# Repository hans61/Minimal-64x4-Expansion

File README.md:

# Minimal-64x4-Expansion

Hardware
https://github.com/hans61/Minimal-64x4-Expansion/tree/main/hardware

Software
https://github.com/hans61/Minimal-64x4-Expansion/tree/main/software

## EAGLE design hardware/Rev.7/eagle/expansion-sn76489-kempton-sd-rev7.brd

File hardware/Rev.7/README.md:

# Minimal-64x4 Expansion Rev.7

Revision 7 extends the previous one with a power ON reset based on a NE555.

Revision 6: https://github.com/hans61/Minimal-64x4-Expansion/tree/main/hardware/Rev.6

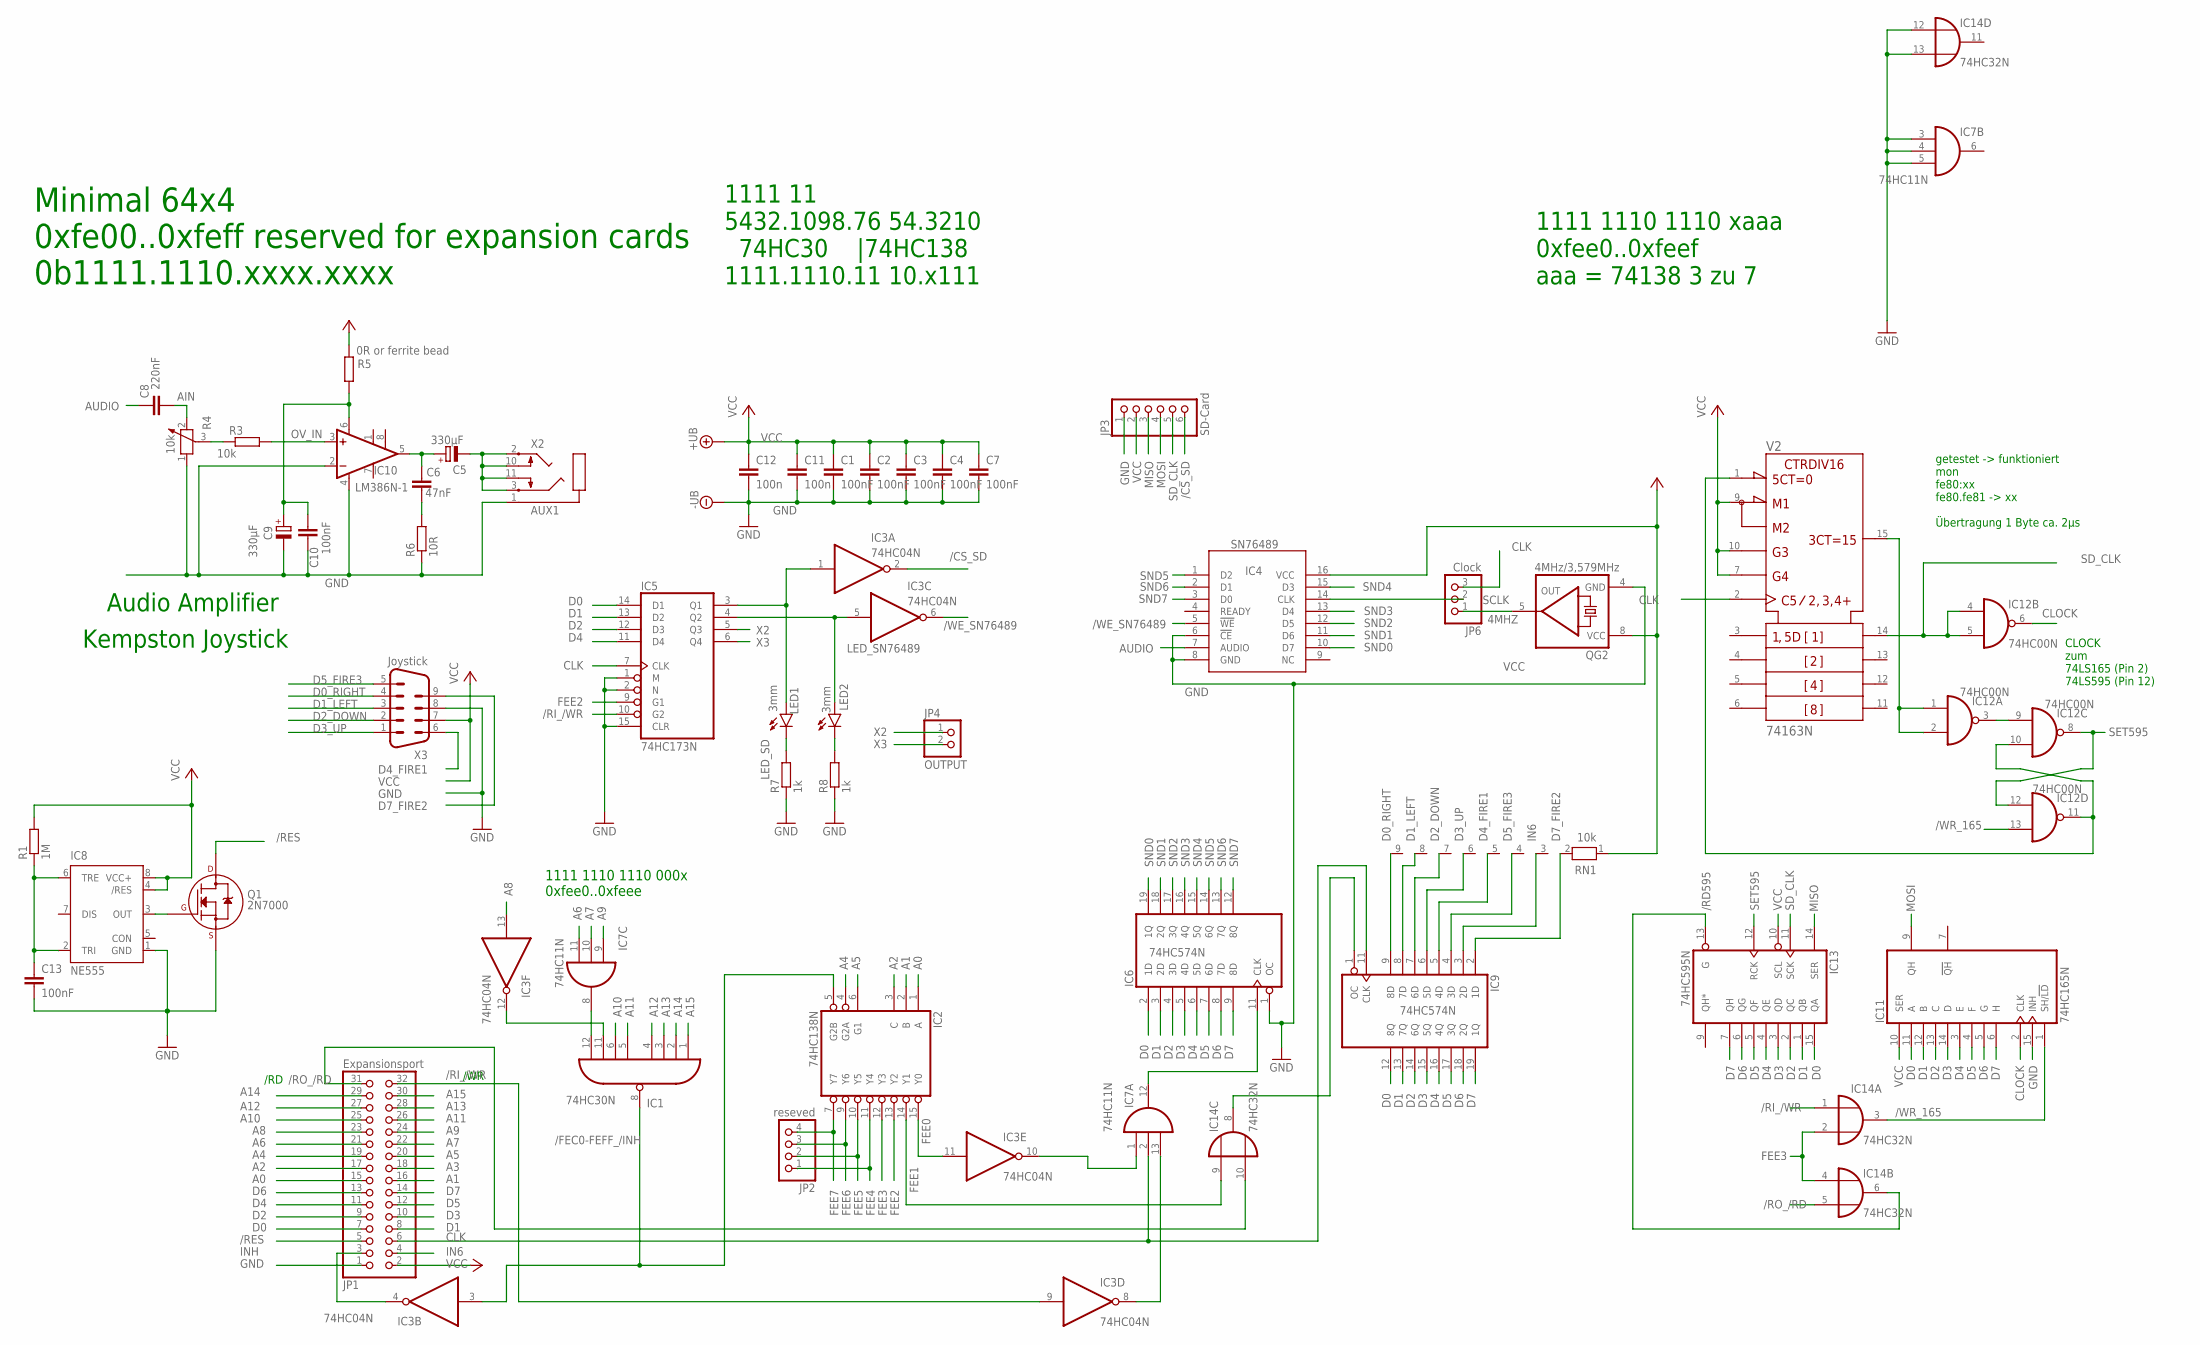
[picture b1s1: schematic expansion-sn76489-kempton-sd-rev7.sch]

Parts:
C1, C2, C3, C4, C7, C10: 100nF; C050-025X075
C5, C9: 330µF; E2,5-7
C6: 47nF; C050-025X075
C8: 220nF; C050-025X075
C11, C12: 100n; C050-025X075
C13: 100nF; C050-030X075
IC1: 74HC30N; DIL14
IC2: 74HC138N; DIL16
IC3: 74HC04N; DIL14
IC4: SN76489; ALEX-PARTS_DIL16
IC5: 74HC173N; DIL16
IC6, IC9: 74HC574N; DIL20
IC7: 74HC11N; DIL14
IC8: NE555; DIL-08
IC10: LM386N-1; DIL08
IC11: 74HC165N; DIL16
IC12: 74HC00N; DIL14
IC13: 74HC595N; DIL16
IC14: 74HC32N; DIL14
JP1: Expansionsport; 2X16
JP2: reseved; 1X04
JP3: SD-Card; 1X06
JP4: OUTPUT; 1X02
JP6: Clock; 1X03
LED1, LED2: 3mm; LED3MM
Q1: 2N7000; TO-92
QG2: 4MHz/3,579MHz; DIL08S
R1: 1M; 0207/10
R3: 10k; 0207/10
R4: 10k; PT-10S
R5: 0R or ferrite bead; 0207/10
R6: 10R; 0207/10
R7, R8: 1k; 0207/2V
RN1: 10k; RN-9
V2: 74163N; DIL16
X2: AUX1; SJ1-352XN
X3: Joystick; 182-009-MALE

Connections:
4MHZ: JP6.1, QG2.5 (OUT)
/CS_SD: IC3.2 (O), JP3.6
/FEC0-FEFF_/INH: IC1.8 (O), IC2.5 (G2B), IC3.3 (I)
/RD595: IC13.13 (G), IC14.6 (O)
/RES: JP1.5, Q1.3 (D)
/RI_/WR: IC3.9 (I), IC5.10 (G2), IC14.1 (I0), JP1.32
/RO_/RD: IC14.5 (I1), IC14.10 (I1), JP1.31
/WE_SN76489: IC3.6 (O), IC4.5 (!WE)
/WR_165: IC11.1 (SH/!LD), IC12.13 (I1), IC14.3 (O)
A0: IC2.1 (A), JP1.15
A1: IC2.2 (B), JP1.16
A2: IC2.3 (C), JP1.17
A3: JP1.18
A4: IC2.4 (G2A), JP1.19
A5: IC2.6 (G1), JP1.20
A6: IC7.11 (I2), JP1.21
A7: IC7.10 (I1), JP1.22
A8: IC3.13 (I), JP1.23
A9: IC7.9 (I0), JP1.24
A10: IC1.6 (I5), JP1.25
A11: IC1.5 (I4), JP1.26
A12: IC1.4 (I3), JP1.27
A13: IC1.3 (I2), JP1.28
A14: IC1.2 (I1), JP1.29
A15: IC1.1 (I0), JP1.30
AIN: C8.2, R4.2
AUDIO: C8.1, IC4.7 (AUDIO)
AUXOUT1: C5.-, X2.2, X2.3, X2.10, X2.11
AVCC: C9.+, C10.1, IC10.6 (VS), R5.1
CLK: IC5.7 (CLK), IC7.2 (I1), IC9.11 (CLK), JP1.6, JP6.3, V2.2 (CLK)
CLOCK: IC11.2 (CLK), IC12.6 (O)
D0: IC5.14 (D1), IC6.2 (1D), IC9.12 (8Q), IC11.11 (A), IC13.15 (QA), JP1.7
D0_RIGHT: IC9.9 (8D), RN1.9, X3.4
D1: IC5.13 (D2), IC6.3 (2D), IC9.13 (7Q), IC11.12 (B), IC13.1 (QB), JP1.8
D1_LEFT: IC9.8 (7D), RN1.8, X3.3
D2: IC5.12 (D3), IC6.4 (3D), IC9.14 (6Q), IC11.13 (C), IC13.2 (QC), JP1.9
D2_DOWN: IC9.7 (6D), RN1.7, X3.2
D3: IC6.5 (4D), IC9.15 (5Q), IC11.14 (D), IC13.3 (QD), JP1.10
D3_UP: IC9.6 (5D), RN1.6, X3.1
D4: IC5.11 (D4), IC6.6 (5D), IC9.16 (4Q), IC11.3 (E), IC13.4 (QE), JP1.11
D4_FIRE1: IC9.5 (4D), RN1.5, X3.6
D5: IC6.7 (6D), IC9.17 (3Q), IC11.4 (F), IC13.5 (QF), JP1.12
D5_FIRE3: IC9.4 (3D), RN1.4, X3.5
D6: IC6.8 (7D), IC9.18 (2Q), IC11.5 (G), IC13.6 (QG), JP1.13
D7: IC6.9 (8D), IC9.19 (1Q), IC11.6 (H), IC13.7 (QH), JP1.14
D7_FIRE2: IC9.2 (1D), RN1.2, X3.9
FEE0: IC2.15 (Y0), IC3.11 (I)
FEE1: IC2.14 (Y1), IC14.9 (I0)
FEE2: IC2.13 (Y2), IC5.9 (G1)
FEE3: IC2.12 (Y3), IC14.2 (I1), IC14.4 (I0)
FEE4: IC2.11 (Y4), JP2.1
FEE5: IC2.10 (Y5), JP2.2
FEE6: IC2.9 (Y6), JP2.3
FEE7: IC2.7 (Y7), JP2.4
GND: C1.2, C2.2, C3.2, C4.2, C7.2, C9.-, C10.2, C11.2, C12.2, C13.2, IC1.7 (GND), IC2.8 (GND), IC3.7 (GND), IC4.6 (!CE), IC4.8 (GND), IC5.1 (M), IC5.2 (N), IC5.8 (GND), IC5.15 (CLR), IC6.1 (OC), IC6.10 (GND), IC7.3 (I0), IC7.4 (I1), IC7.5 (I2), IC7.7 (GND), IC8.1 (GND), IC9.10 (GND), IC10.2 (-IN), IC10.4 (GND), IC11.8 (GND), IC11.15 (INH), IC12.7 (GND), IC13.8 (GND), IC14.7 (GND), IC14.12 (I0), IC14.13 (I1), JP1.1, JP3.1, Q1.1 (S), QG2.4 (GND), R4.1, R6.1, R7.1, R8.1, V2.8 (-UB), X2.1, X3.8
IN6: IC9.3 (2D), JP1.4, RN1.3
INH: IC3.4 (O), JP1.3
INPUT_EN: IC9.1 (OC), IC14.8 (O)
LED_SD: IC3.1 (I), IC5.3 (Q1), LED1.A
LED_SN76489: IC3.5 (I), IC5.4 (Q2), LED2.A
MISO: IC13.14 (SER), JP3.3
MOSI: IC11.9 (QH), JP3.4
unnamed: LED2.K (C), R8.2
unnamed: IC3.10 (O), IC7.1 (I0)
unnamed: IC1.12 (I7), IC7.8 (O)
unnamed: C13.1, IC8.2 (TRI), IC8.6 (TRE), R1.1
unnamed: IC8.3 (OUT), Q1.2 (G)
unnamed: C6.2, R6.2
unnamed: IC12.1 (I0), IC12.2 (I1), V2.15 (RCO)
unnamed: R3.1, R4.3
unnamed: IC12.10 (I1), IC12.11 (O), V2.1 (!CLR)
unnamed: IC12.3 (O), IC12.9 (I0)
unnamed: LED1.K (C), R7.2
unnamed: IC1.11 (I6), IC3.12 (O)
OV_IN: IC10.3 (+IN), R3.2
R2C2C3: C5.+, C6.1, IC10.5 (OUT)
RI_WR: IC3.8 (O), IC7.13 (I2)
SCLK: IC4.14 (CLK), JP6.2
SD_CLK: IC12.4 (I0), IC12.5 (I1), IC13.11 (SCK), JP3.5, V2.14 (QA)
SET595: IC12.8 (O), IC12.12 (I0), IC13.12 (RCK)
SND0: IC4.10 (D7), IC6.19 (1Q)
SND1: IC4.11 (D6), IC6.18 (2Q)
SND2: IC4.12 (D5), IC6.17 (3Q)
SND3: IC4.13 (D4), IC6.16 (4Q)
SND4: IC4.15 (D3), IC6.15 (5Q)
SND5: IC4.1 (D2), IC6.14 (6Q)
SND6: IC4.2 (D1), IC6.13 (7Q)
SND7: IC4.3 (D0), IC6.12 (8Q)
SOUND_EN: IC6.11 (CLK), IC7.12 (O)
VCC: C1.1, C2.1, C3.1, C4.1, C7.1, C11.1, C12.1, IC1.14 (VCC), IC2.16 (VCC), IC3.14 (VCC), IC4.16 (VCC), IC5.16 (VCC), IC6.20 (VCC), IC7.14 (VCC), IC8.4 (/RES), IC8.8 (VCC+), IC9.20 (VCC), IC11.10 (SER), IC11.16 (VCC), IC12.14 (VCC), IC13.10 (SCL), IC13.16 (VCC), IC14.14 (VCC), JP1.2, JP3.2, QG2.8 (VCC), R1.2, R5.2, RN1.1, V2.7 (ENP), V2.9 (!LOAD), V2.10 (ENT), V2.16 (+UB), X3.7
X2: IC5.5 (Q3), JP4.1
X3: IC5.6 (Q4), JP4.2

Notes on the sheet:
1111 1110 1110 xaaa 0xfee0..0xfeef aaa = 74138 3 zu 7
1111 1110 1110 000x 0xfee0..0xfeee
/WR
/RD
Minimal 64x4 0xfe00..0xfeff reserved for expansion cards 0b1111.1110.xxxx.xxxx
1111 11 5432.1098.76 54.3210 74HC30 |74HC138 1111.1110.11 10.x111
Kempston Joystick
Audio Amplifier
CLOCK zum 74LS165 (Pin 2) 74LS595 (Pin 12)
getestet -> funktioniert mon fe80:xx fe80.fe81 -> xx Übertragung 1 Byte ca. 2µs

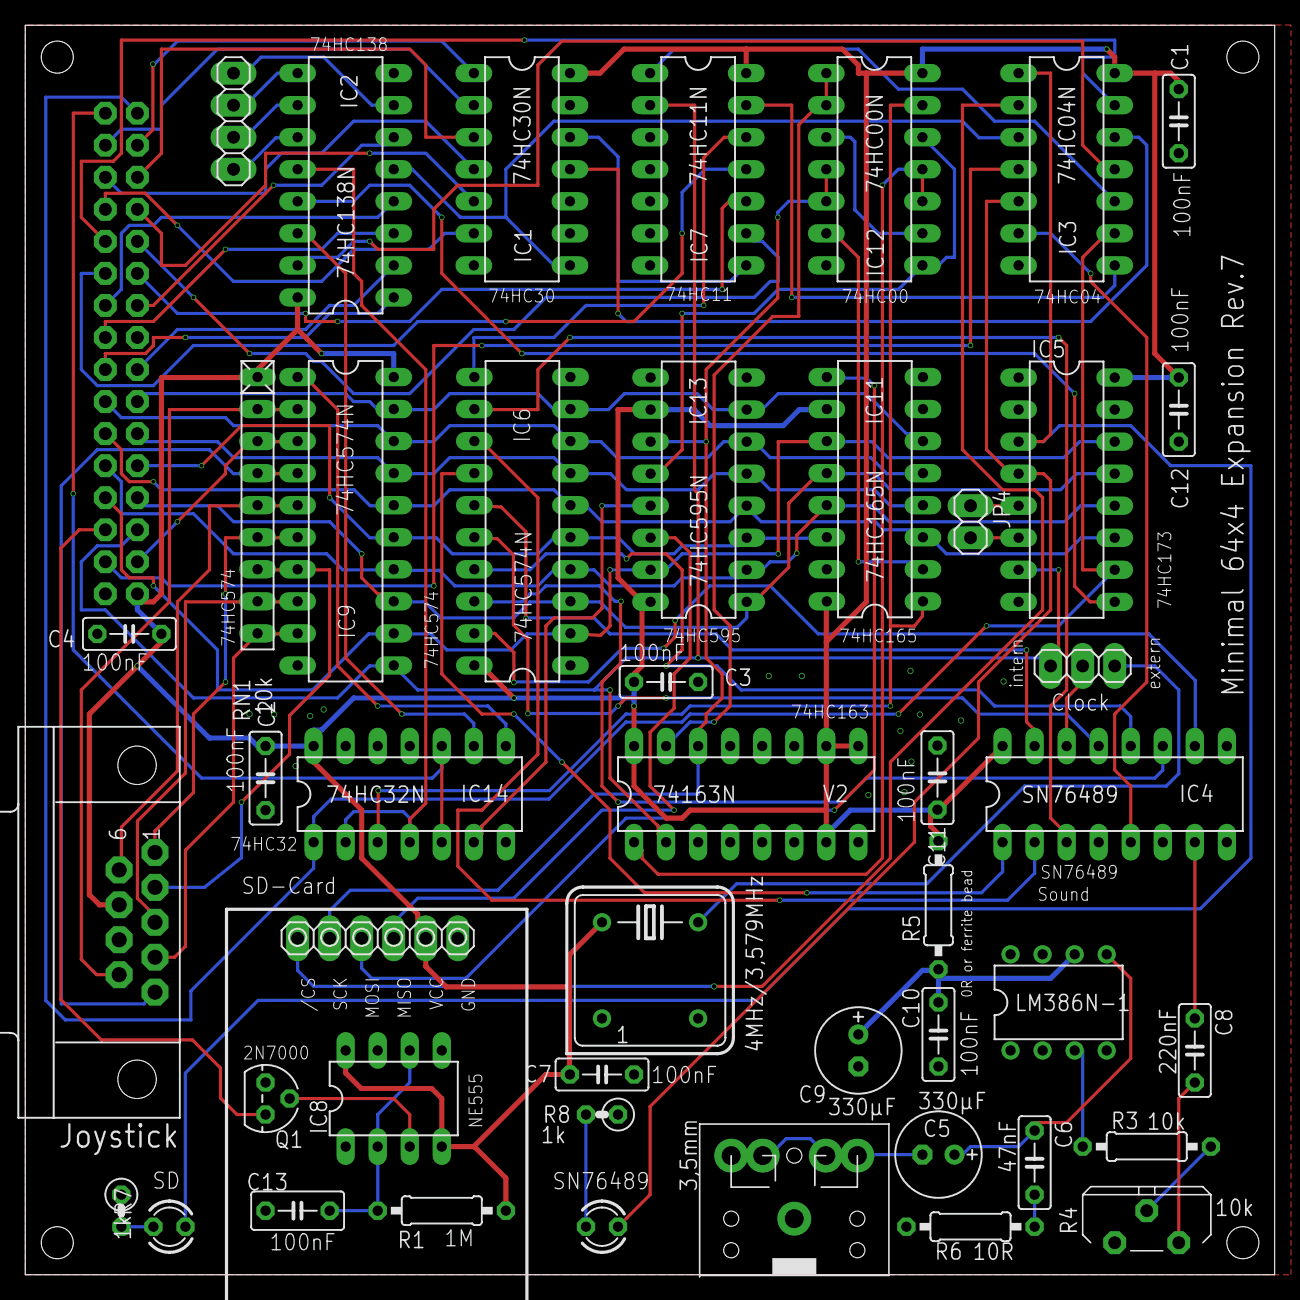
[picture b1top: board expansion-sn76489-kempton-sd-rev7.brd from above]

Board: 2 copper layers, 99.0 x 99.0 mm, 47 parts (1 on the bottom side), 91 nets.

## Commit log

2025-01-12 first files
2025-03-06 revision 7 of the expansion board
2025-03-07 add picture
2025-03-07 add vsync test
2025-04-18 Examples for SN76489 added
2025-04-18 More software added
2025-04-18 vsync instructions
2025-04-18 added picture
